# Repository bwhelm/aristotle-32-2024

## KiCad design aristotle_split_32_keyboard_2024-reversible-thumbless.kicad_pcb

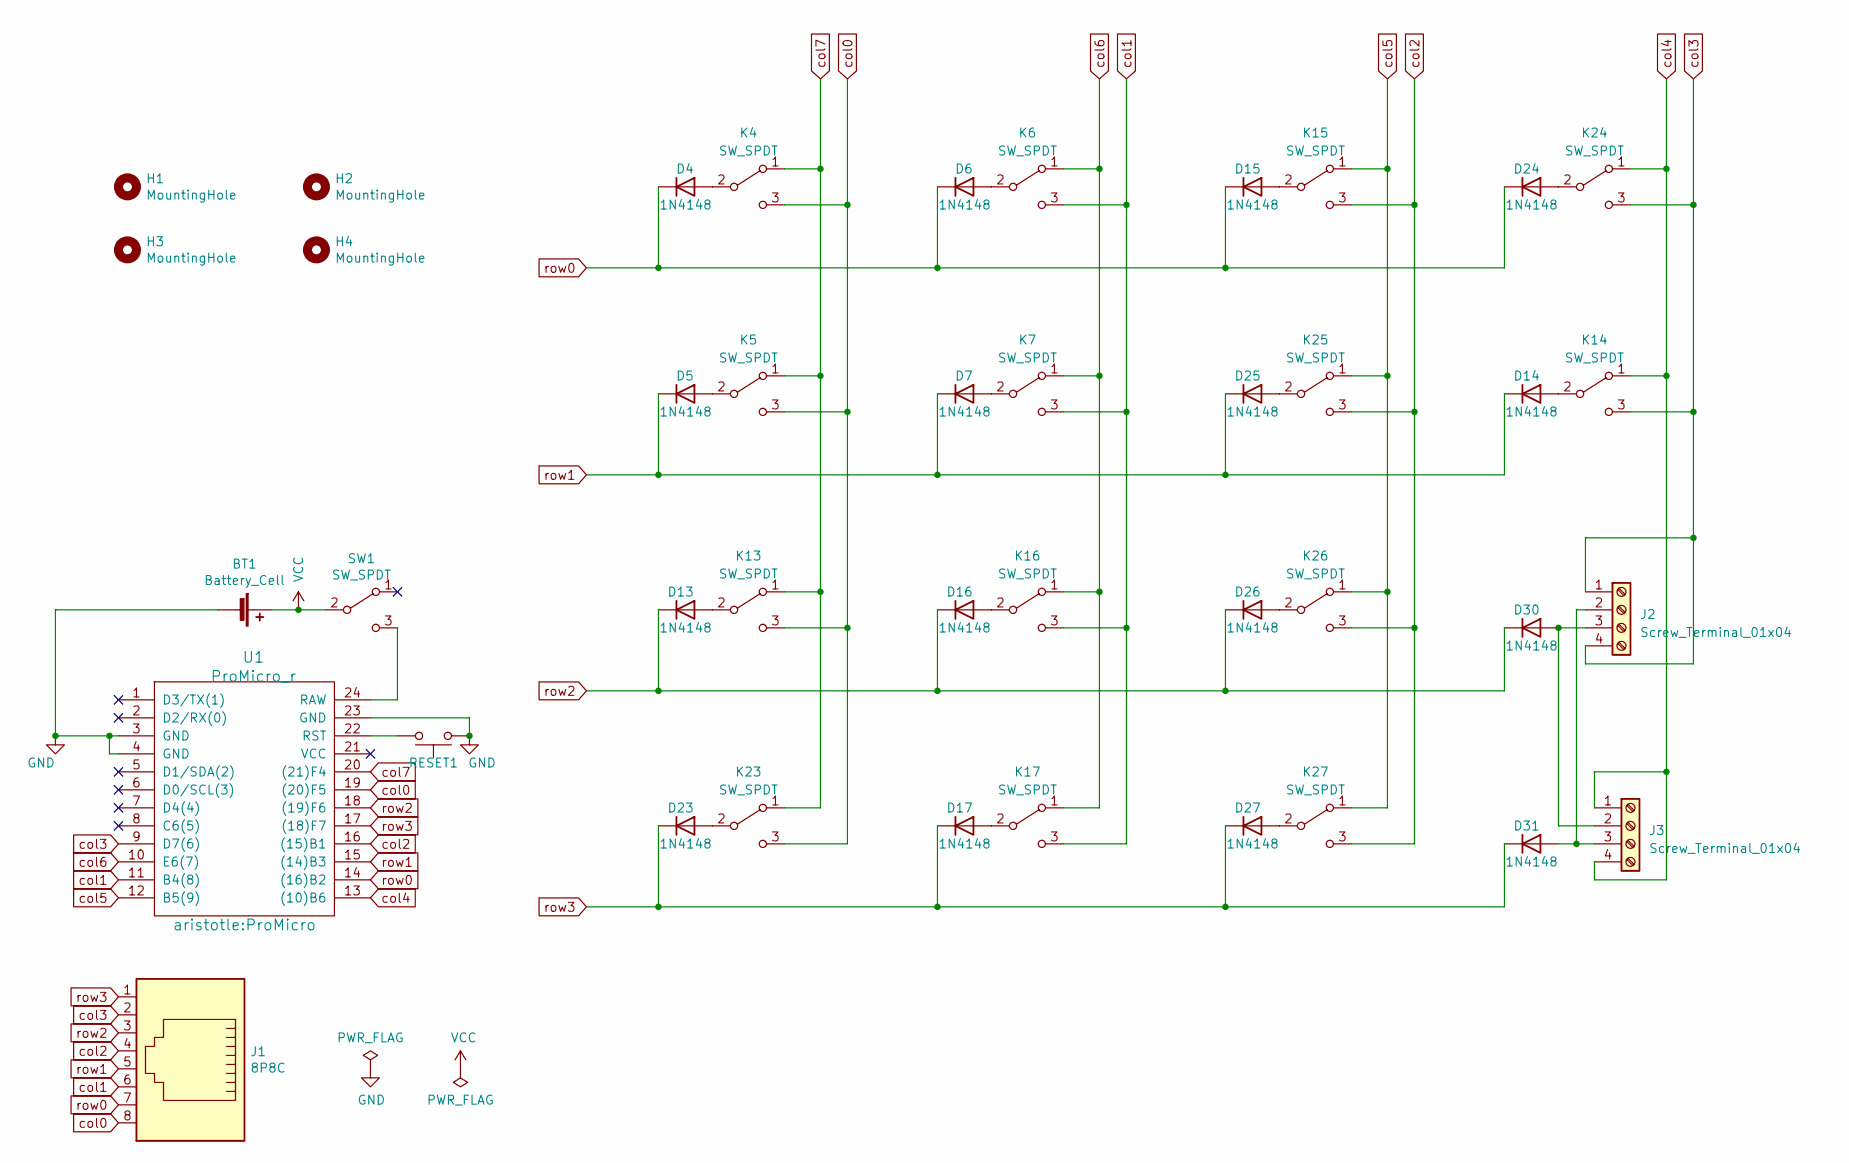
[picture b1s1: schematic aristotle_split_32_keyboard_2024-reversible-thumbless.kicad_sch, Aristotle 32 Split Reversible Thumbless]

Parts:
BT1: Battery_Cell; D_1210_3225Metric
D4, D5, D6, D7, D13, D14, D15, D16, D17, D23, D24, D25, D26, D27, D30, D31: 1N4148; D_T-1_P5.08mm_Horizontal-NO_B.SILK
H1, H2, H3, H4: MountingHole; MountingHole_2.2mm_M2
J1: 8P8C; RJ45_Amphenol_54602-x08_Horizontal-DOUBLE
J2, J3: Screw_Terminal_01x04; TerminalBlock_Phoenix_MPT-0,5-4-2.54_1x04_P2.54mm_Horizontal
K4, K5, K6, K7, K13, K14, K15, K16, K17, K23, K24, K25, K26, K27: SW_SPDT; Kailh-Choc_1350-Keyswitch-mirrored
RESET1: SW_PUSH_6mm
SW1: SW_SPDT; SW_CuK_OS102011MA1QN1_SPDT_Angled
U1: ProMicro_r; ProMicro

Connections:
GND: BT1.2 (-), RESET1.1, U1.3 (GND), U1.4 (GND), U1.23 (GND)
unnamed: D4.2 (A), K4.2 (B)
unnamed: D5.2 (A), K5.2 (B)
unnamed: D6.2 (A), K6.2 (B)
unnamed: D7.2 (A), K7.2 (B)
unnamed: D13.2 (A), K13.2 (B)
unnamed: D14.2 (A), K14.2 (B)
unnamed: D15.2 (A), K15.2 (B)
unnamed: D16.2 (A), K16.2 (B)
unnamed: D17.2 (A), K17.2 (B)
unnamed: D23.2 (A), K23.2 (B)
unnamed: D24.2 (A), K24.2 (B)
unnamed: D25.2 (A), K25.2 (B)
unnamed: D26.2 (A), K26.2 (B)
unnamed: D27.2 (A), K27.2 (B)
unnamed: D30.2 (A), J2.3, J3.2
unnamed: D31.2 (A), J2.2, J3.3
unnamed: SW1.3 (C), U1.24 (RAW)
unnamed: RESET1.2, U1.22 (RST)
VCC: BT1.1 (+), SW1.2 (B)
col0: J1.8, K4.3 (C), K5.3 (C), K13.3 (C), K23.3 (C), U1.19 ((20)F5)
col1: J1.6, K6.3 (C), K7.3 (C), K16.3 (C), K17.3 (C), U1.11 (B4(8))
col2: J1.4, K15.3 (C), K25.3 (C), K26.3 (C), K27.3 (C), U1.16 ((15)B1)
col3: J1.2, J2.1, J2.4, K14.3 (C), K24.3 (C), U1.9 (D7(6))
col4: J3.1, J3.4, K14.1 (A), K24.1 (A), U1.13 ((10)B6)
col5: K15.1 (A), K25.1 (A), K26.1 (A), K27.1 (A), U1.12 (B5(9))
col6: K6.1 (A), K7.1 (A), K16.1 (A), K17.1 (A), U1.10 (E6(7))
col7: K4.1 (A), K5.1 (A), K13.1 (A), K23.1 (A), U1.20 ((21)F4)
row0: D4.1 (K), D6.1 (K), D15.1 (K), D24.1 (K), J1.7, U1.14 ((16)B2)
row1: D5.1 (K), D7.1 (K), D14.1 (K), D25.1 (K), J1.5, U1.15 ((14)B3)
row2: D13.1 (K), D16.1 (K), D26.1 (K), D30.1 (K), J1.3, U1.18 ((19)F6)
row3: D17.1 (K), D23.1 (K), D27.1 (K), D31.1 (K), J1.1, U1.17 ((18)F7)

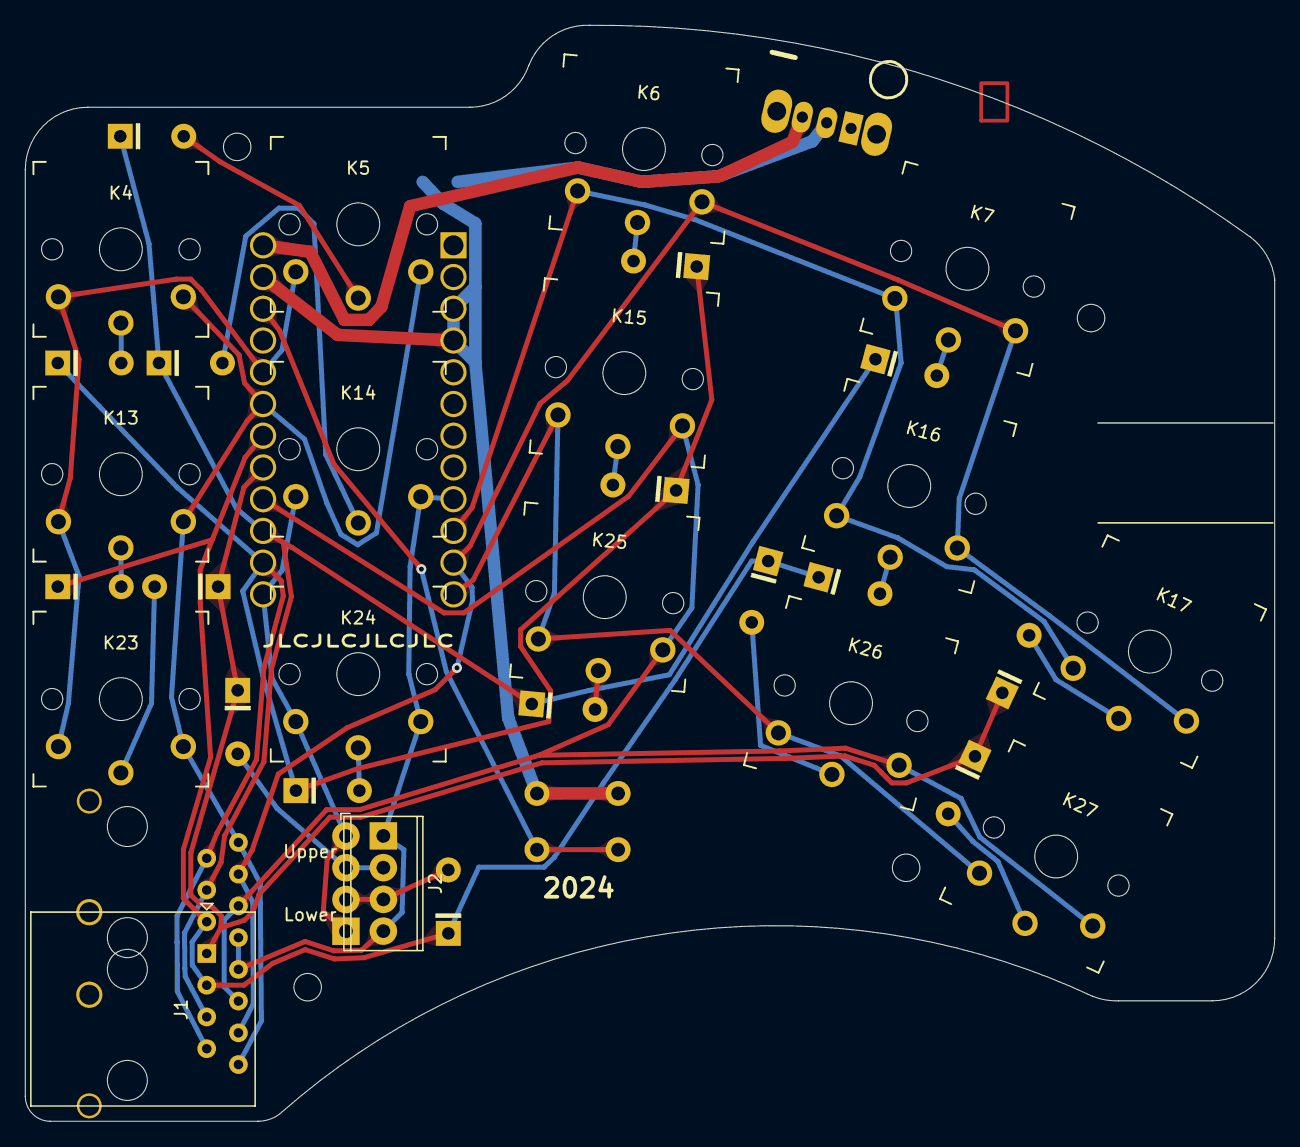
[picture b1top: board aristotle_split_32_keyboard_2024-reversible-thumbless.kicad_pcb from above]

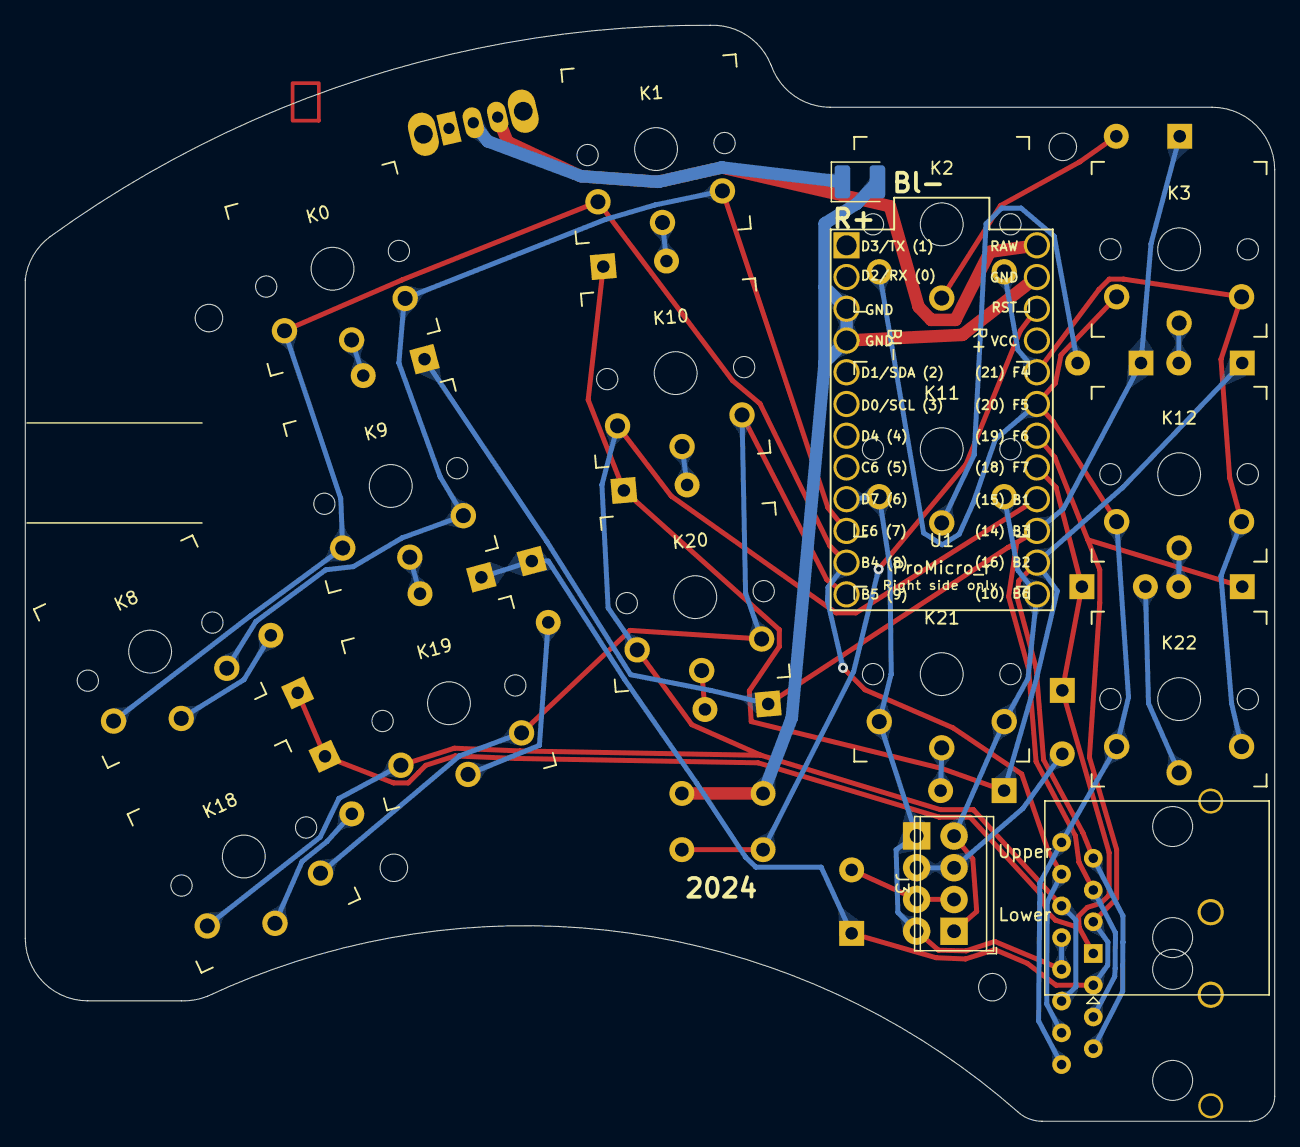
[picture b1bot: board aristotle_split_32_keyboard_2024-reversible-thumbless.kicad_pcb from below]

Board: 2 copper layers, 100.0 x 87.7 mm, 41 parts (3 on the bottom side), 32 nets.

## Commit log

2024-03-13 Add license
2024-03-13 Remove unneeded libraries
2024-03-14 Move MCU up; reroute all wires to it; adjust screw positions
2024-03-14 Fix mounting holes
2024-03-15 Adjust diode positions; move battery attachment pad
2024-03-16 Reroute tracks, making default width .4 mm
2024-03-18 More rerouting
2024-03-20 Reassign MCU pins to rows/columns
2024-03-21 Move pins; update symbol library with pin numbers
2024-03-23 Final production version
